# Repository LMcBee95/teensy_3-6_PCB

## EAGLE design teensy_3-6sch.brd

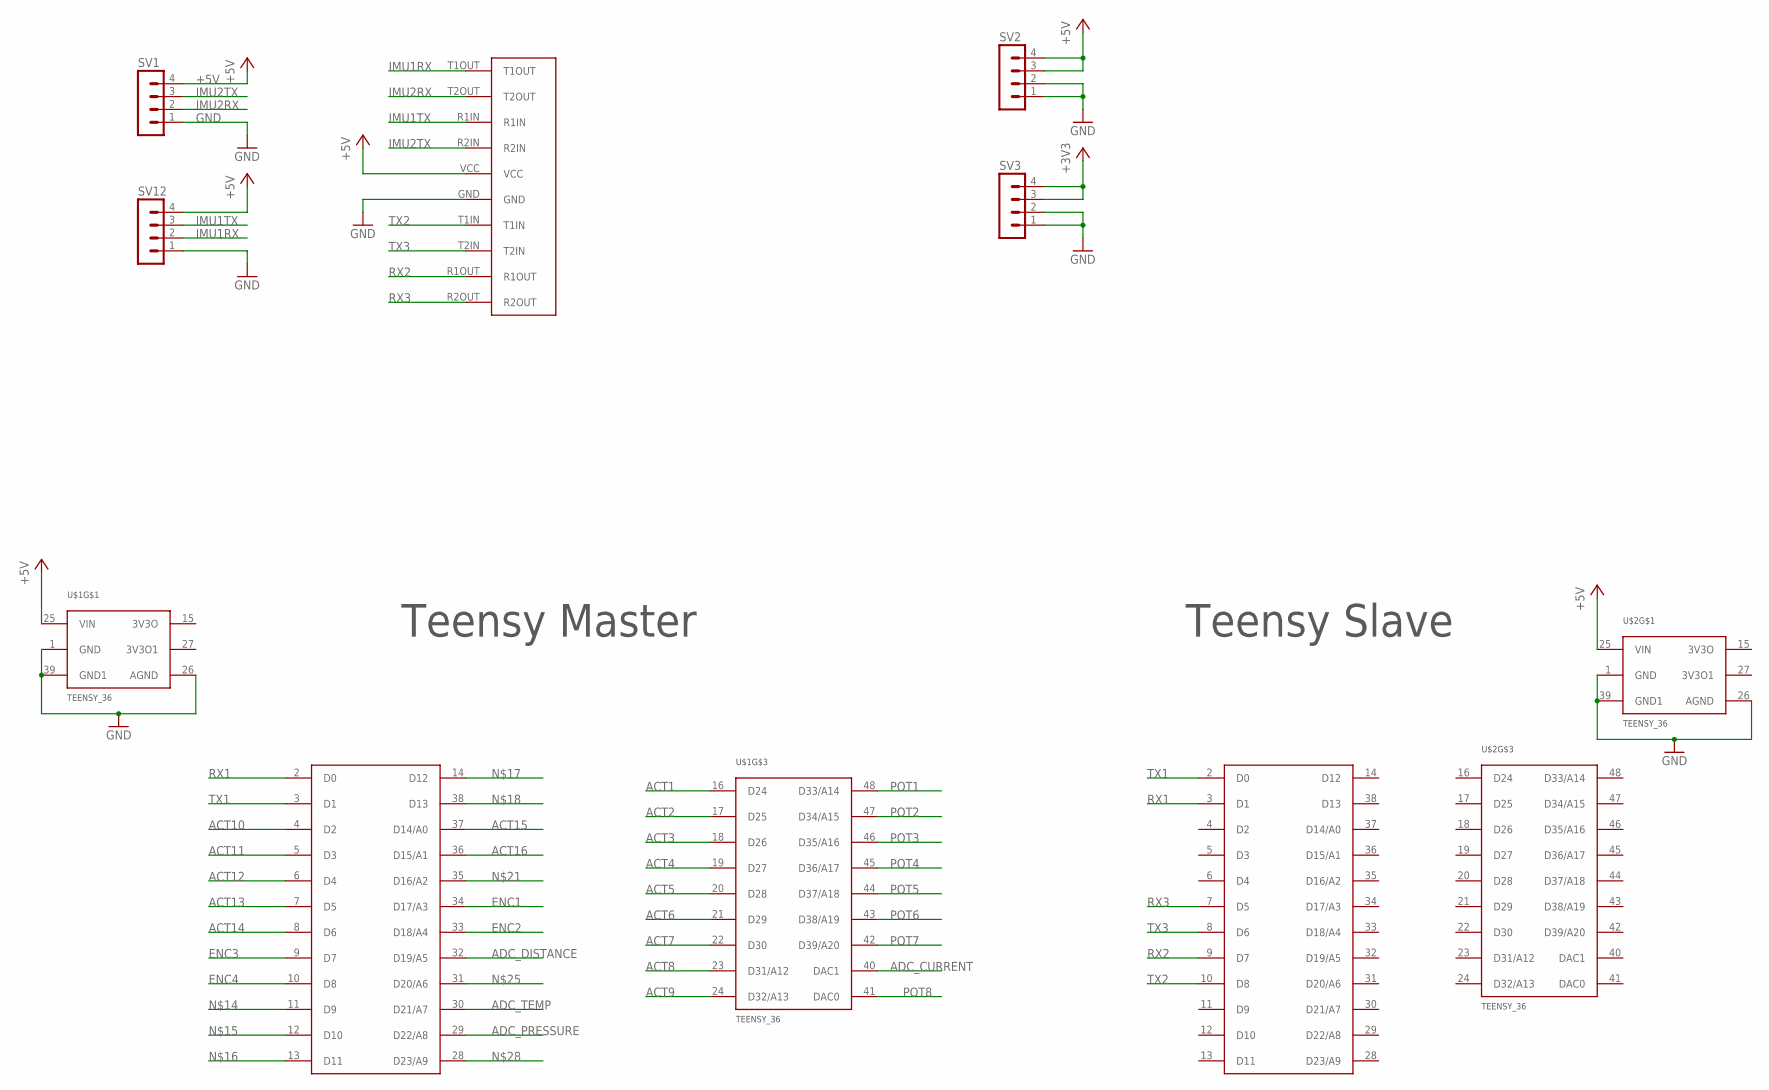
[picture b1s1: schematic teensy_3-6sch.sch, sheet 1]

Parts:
SV1, SV2, SV3, SV12: MA04-1
U$1, U$2: TEENSY_36; TEENSY36
U$3: MAX232_BREAKOUT

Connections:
+3V3: SV3.3, SV3.4; also elsewhere on the board
+5V: SV1.4, SV2.3, SV2.4, SV12.4, U$1.25 (VIN), U$2.25 (VIN), U$3.VCC; also elsewhere on the board
ACT1: U$1.16 (D24); also elsewhere on the board
ACT2: U$1.17 (D25); also elsewhere on the board
ACT3: U$1.18 (D26); also elsewhere on the board
ACT4: U$1.19 (D27); also elsewhere on the board
ACT5: U$1.20 (D28); also elsewhere on the board
ACT6: U$1.21 (D29); also elsewhere on the board
ACT7: U$1.22 (D30); also elsewhere on the board
ACT8: U$1.23 (D31/A12); also elsewhere on the board
ACT9: U$1.24 (D32/A13); also elsewhere on the board
ACT10: U$1.4 (D2); also elsewhere on the board
ACT11: U$1.5 (D3); also elsewhere on the board
ACT12: U$1.6 (D4); also elsewhere on the board
ACT13: U$1.7 (D5); also elsewhere on the board
ACT14: U$1.8 (D6); also elsewhere on the board
ACT15: U$1.37 (D14/A0); also elsewhere on the board
ACT16: U$1.36 (D15/A1); also elsewhere on the board
ADC_CURRENT: U$1.40 (DAC1); also elsewhere on the board
ADC_DISTANCE: U$1.32 (D19/A5); also elsewhere on the board
ADC_PRESSURE: U$1.29 (D22/A8); also elsewhere on the board
ADC_TEMP: U$1.30 (D21/A7); also elsewhere on the board
ENC1: U$1.34 (D17/A3); also elsewhere on the board
ENC2: U$1.33 (D18/A4); also elsewhere on the board
ENC3: U$1.9 (D7); also elsewhere on the board
ENC4: U$1.10 (D8); also elsewhere on the board
GND: SV1.1, SV2.1, SV2.2, SV3.1, SV3.2, SV12.1, U$1.1 (GND), U$1.26 (AGND), U$1.39 (GND1), U$2.1 (GND), U$2.26 (AGND), U$2.39 (GND1), U$3.GND; also elsewhere on the board
IMU1RX: SV12.2, U$3.T1OUT
IMU1TX: SV12.3, U$3.R1IN
IMU2RX: SV1.2, U$3.T2OUT
IMU2TX: SV1.3, U$3.R2IN
POT1: U$1.48 (D33/A14); also elsewhere on the board
POT2: U$1.47 (D34/A15); also elsewhere on the board
POT3: U$1.46 (D35/A16); also elsewhere on the board
POT4: U$1.45 (D36/A17); also elsewhere on the board
POT5: U$1.44 (D37/A18); also elsewhere on the board
POT6: U$1.43 (D38/A19); also elsewhere on the board
POT7: U$1.42 (D39/A20); also elsewhere on the board
POT8: U$1.41 (DAC0); also elsewhere on the board
RX1: U$1.2 (D0), U$2.3 (D1)
RX2: U$2.9 (D7), U$3.R1OUT
RX3: U$2.7 (D5), U$3.R2OUT
TX1: U$1.3 (D1), U$2.2 (D0)
TX2: U$2.10 (D8), U$3.T1IN
TX3: U$2.8 (D6), U$3.T2IN

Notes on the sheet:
Teensy Master
Teensy Slave

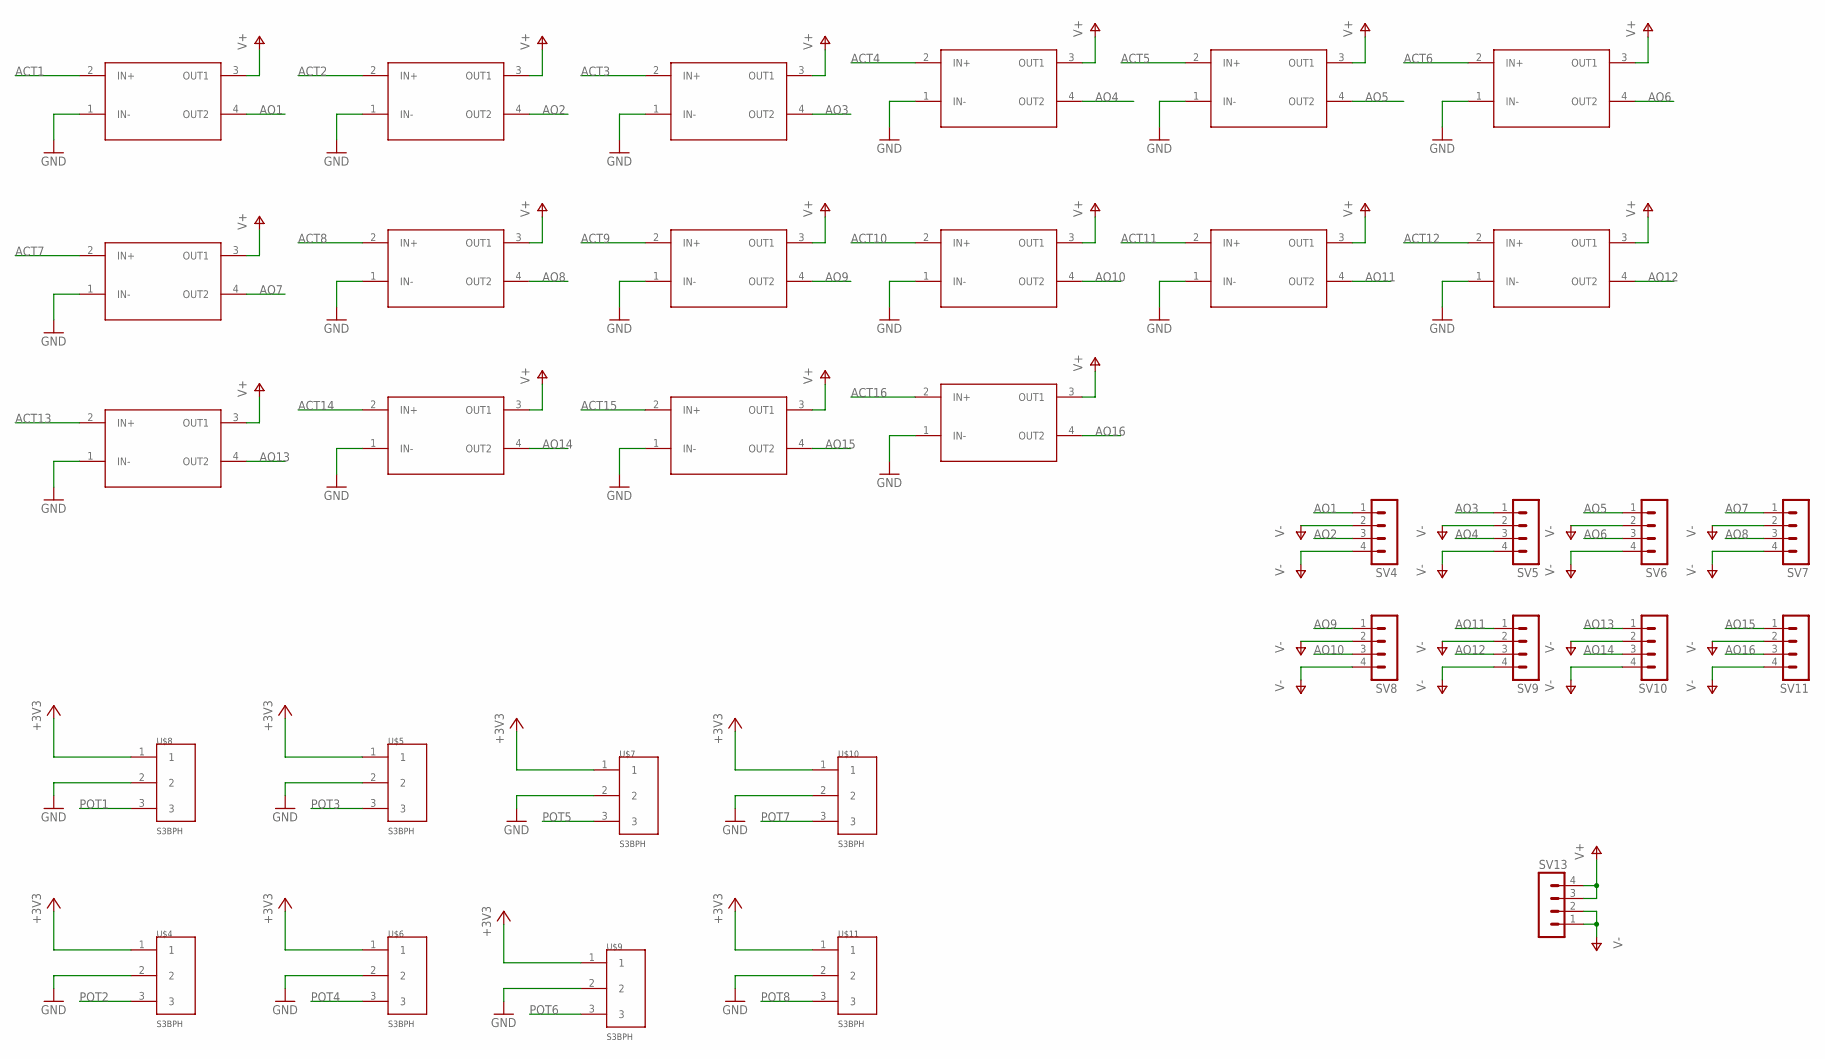
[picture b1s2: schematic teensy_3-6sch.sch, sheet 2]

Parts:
SV4, SV5, SV6, SV7, SV8, SV9, SV10, SV11, SV13: MA04-1
U$4, U$5, U$6, U$7, U$8, U$9, U$10, U$11: S3BPH
U$12, U$13, U$14, U$15, U$16, U$17, U$18, U$19, U$20, U$21, U$22, U$23, U$24, U$25, U$26, U$27: CPC1706

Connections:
+3V3: U$4.1, U$5.1, U$6.1, U$7.1, U$8.1, U$9.1, U$10.1, U$11.1; also elsewhere on the board
ACT1: U$12.2 (IN+); also elsewhere on the board
ACT2: U$13.2 (IN+); also elsewhere on the board
ACT3: U$14.2 (IN+); also elsewhere on the board
ACT4: U$15.2 (IN+); also elsewhere on the board
ACT5: U$16.2 (IN+); also elsewhere on the board
ACT6: U$17.2 (IN+); also elsewhere on the board
ACT7: U$18.2 (IN+); also elsewhere on the board
ACT8: U$19.2 (IN+); also elsewhere on the board
ACT9: U$20.2 (IN+); also elsewhere on the board
ACT10: U$21.2 (IN+); also elsewhere on the board
ACT11: U$22.2 (IN+); also elsewhere on the board
ACT12: U$23.2 (IN+); also elsewhere on the board
ACT13: U$24.2 (IN+); also elsewhere on the board
ACT14: U$25.2 (IN+); also elsewhere on the board
ACT15: U$26.2 (IN+); also elsewhere on the board
ACT16: U$27.2 (IN+); also elsewhere on the board
AO1: SV4.1, U$12.4 (OUT2)
AO2: SV4.3, U$13.4 (OUT2)
AO3: SV5.1, U$14.4 (OUT2)
AO4: SV5.3, U$15.4 (OUT2)
AO5: SV6.1, U$16.4 (OUT2)
AO6: SV6.3, U$17.4 (OUT2)
AO7: SV7.1, U$18.4 (OUT2)
AO8: SV7.3, U$19.4 (OUT2)
AO9: SV8.1, U$20.4 (OUT2)
AO10: SV8.3, U$21.4 (OUT2)
AO11: SV9.1, U$22.4 (OUT2)
AO12: SV9.3, U$23.4 (OUT2)
AO13: SV10.1, U$24.4 (OUT2)
AO14: SV10.3, U$25.4 (OUT2)
AO15: SV11.1, U$26.4 (OUT2)
AO16: SV11.3, U$27.4 (OUT2)
GND: U$4.2, U$5.2, U$6.2, U$7.2, U$8.2, U$9.2, U$10.2, U$11.2, U$12.1 (IN-), U$13.1 (IN-), U$14.1 (IN-), U$15.1 (IN-), U$16.1 (IN-), U$17.1 (IN-), U$18.1 (IN-), U$19.1 (IN-), U$20.1 (IN-), U$21.1 (IN-), U$22.1 (IN-), U$23.1 (IN-), U$24.1 (IN-), U$25.1 (IN-), U$26.1 (IN-), U$27.1 (IN-); also elsewhere on the board
POT1: U$8.3; also elsewhere on the board
POT2: U$4.3; also elsewhere on the board
POT3: U$5.3; also elsewhere on the board
POT4: U$6.3; also elsewhere on the board
POT5: U$7.3; also elsewhere on the board
POT6: U$9.3; also elsewhere on the board
POT7: U$10.3; also elsewhere on the board
POT8: U$11.3; also elsewhere on the board
V+: SV13.3, SV13.4, U$12.3 (OUT1), U$13.3 (OUT1), U$14.3 (OUT1), U$15.3 (OUT1), U$16.3 (OUT1), U$17.3 (OUT1), U$18.3 (OUT1), U$19.3 (OUT1), U$20.3 (OUT1), U$21.3 (OUT1), U$22.3 (OUT1), U$23.3 (OUT1), U$24.3 (OUT1), U$25.3 (OUT1), U$26.3 (OUT1), U$27.3 (OUT1)
V-: SV4.2, SV4.4, SV5.2, SV5.4, SV6.2, SV6.4, SV7.2, SV7.4, SV8.2, SV8.4, SV9.2, SV9.4, SV10.2, SV10.4, SV11.2, SV11.4, SV13.1, SV13.2

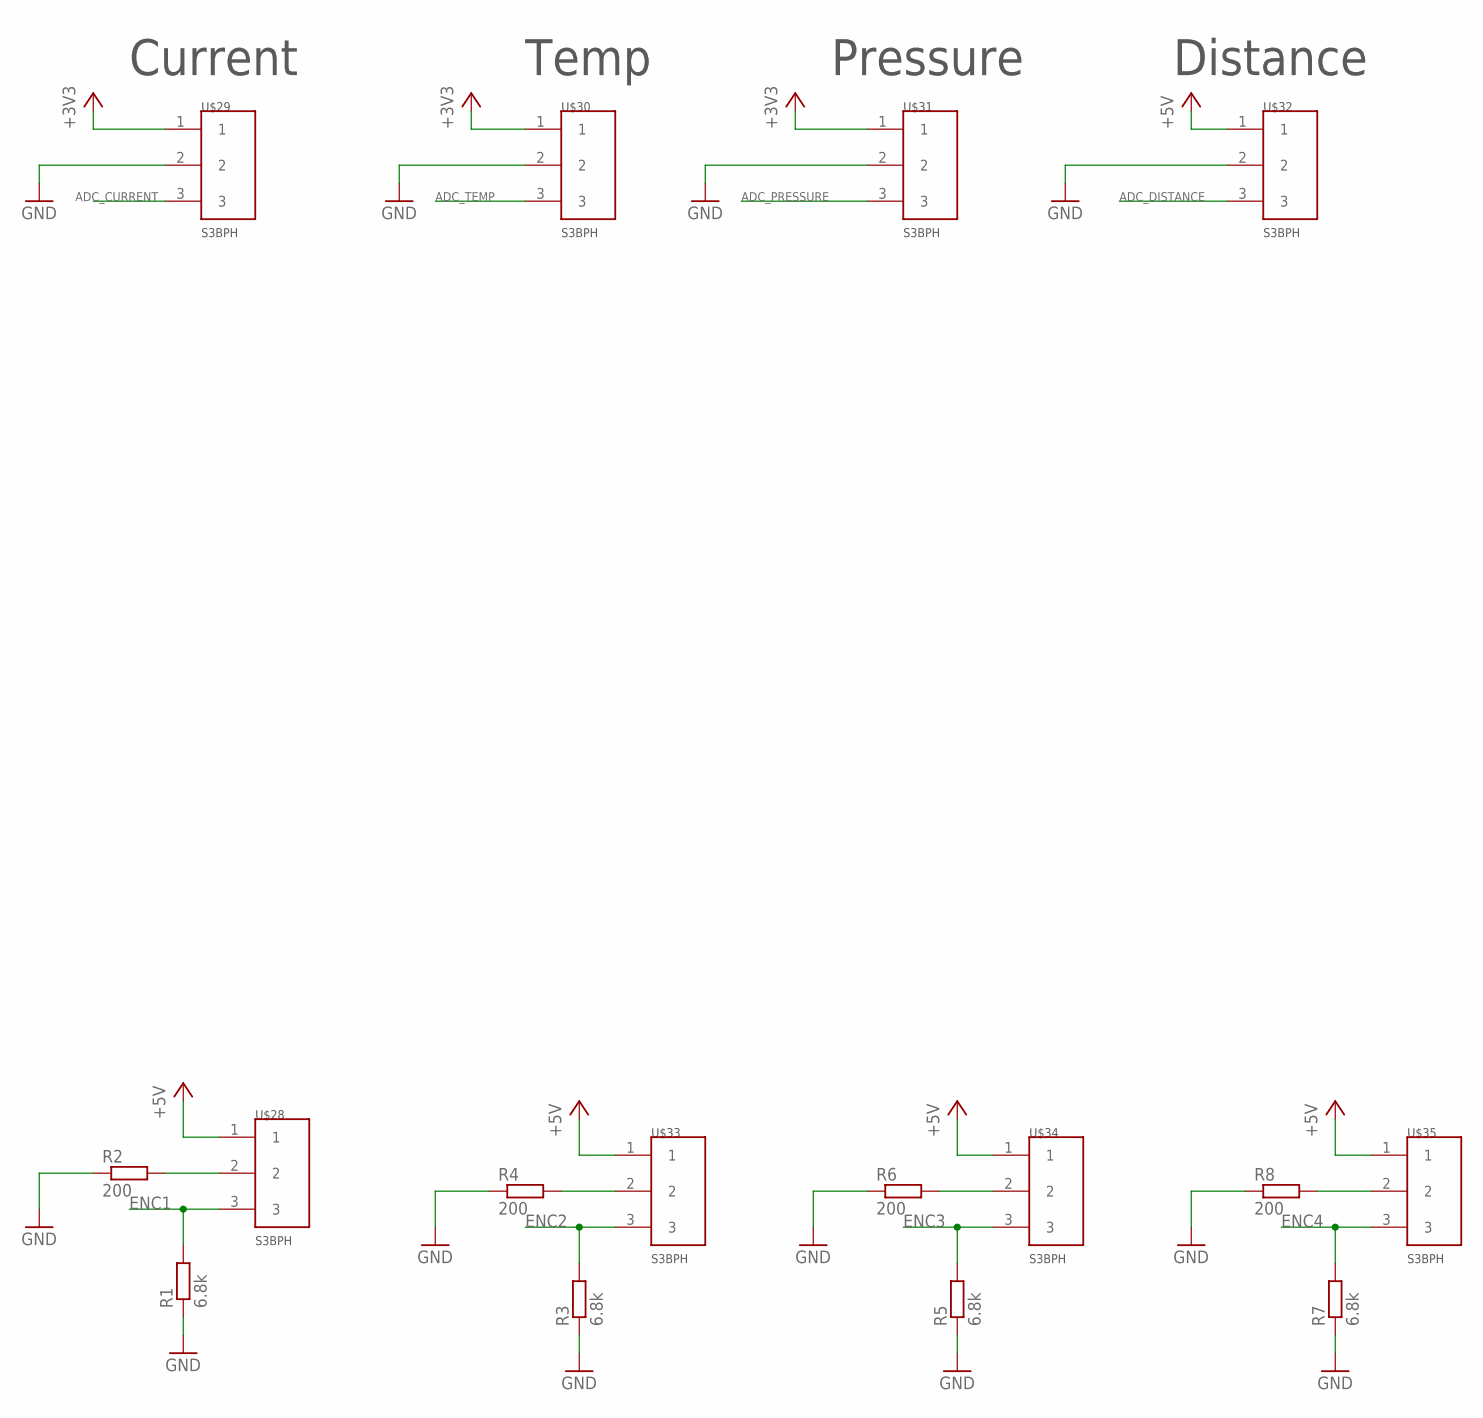
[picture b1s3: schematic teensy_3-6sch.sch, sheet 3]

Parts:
R1, R3, R5, R7: 6.8k; M0805
R2, R4, R6, R8: 200; M0805
U$28, U$29, U$30, U$31, U$32, U$33, U$34, U$35: S3BPH

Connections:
+3V3: U$29.1, U$30.1, U$31.1; also elsewhere on the board
+5V: U$28.1, U$32.1, U$33.1, U$34.1, U$35.1; also elsewhere on the board
ADC_CURRENT: U$29.3; also elsewhere on the board
ADC_DISTANCE: U$32.3; also elsewhere on the board
ADC_PRESSURE: U$31.3; also elsewhere on the board
ADC_TEMP: U$30.3; also elsewhere on the board
ENC1: R1.2, U$28.3; also elsewhere on the board
ENC2: R3.2, U$33.3; also elsewhere on the board
ENC3: R5.2, U$34.3; also elsewhere on the board
ENC4: R7.2, U$35.3; also elsewhere on the board
GND: R1.1, R2.1, R3.1, R4.1, R5.1, R6.1, R7.1, R8.1, U$29.2, U$30.2, U$31.2, U$32.2; also elsewhere on the board
unnamed: R2.2, U$28.2
unnamed: R4.2, U$33.2
unnamed: R6.2, U$34.2
unnamed: R8.2, U$35.2

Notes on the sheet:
Current
Temp
Pressure
Distance

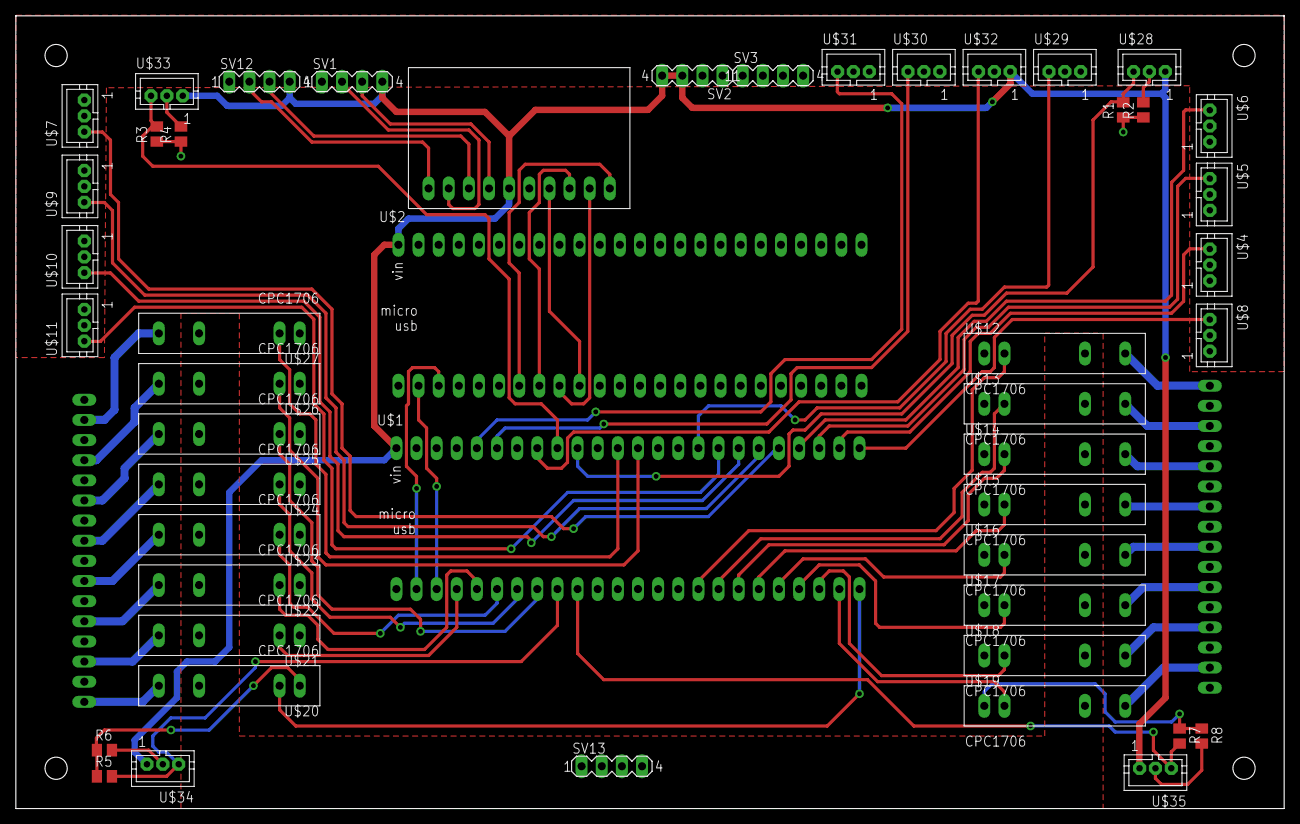
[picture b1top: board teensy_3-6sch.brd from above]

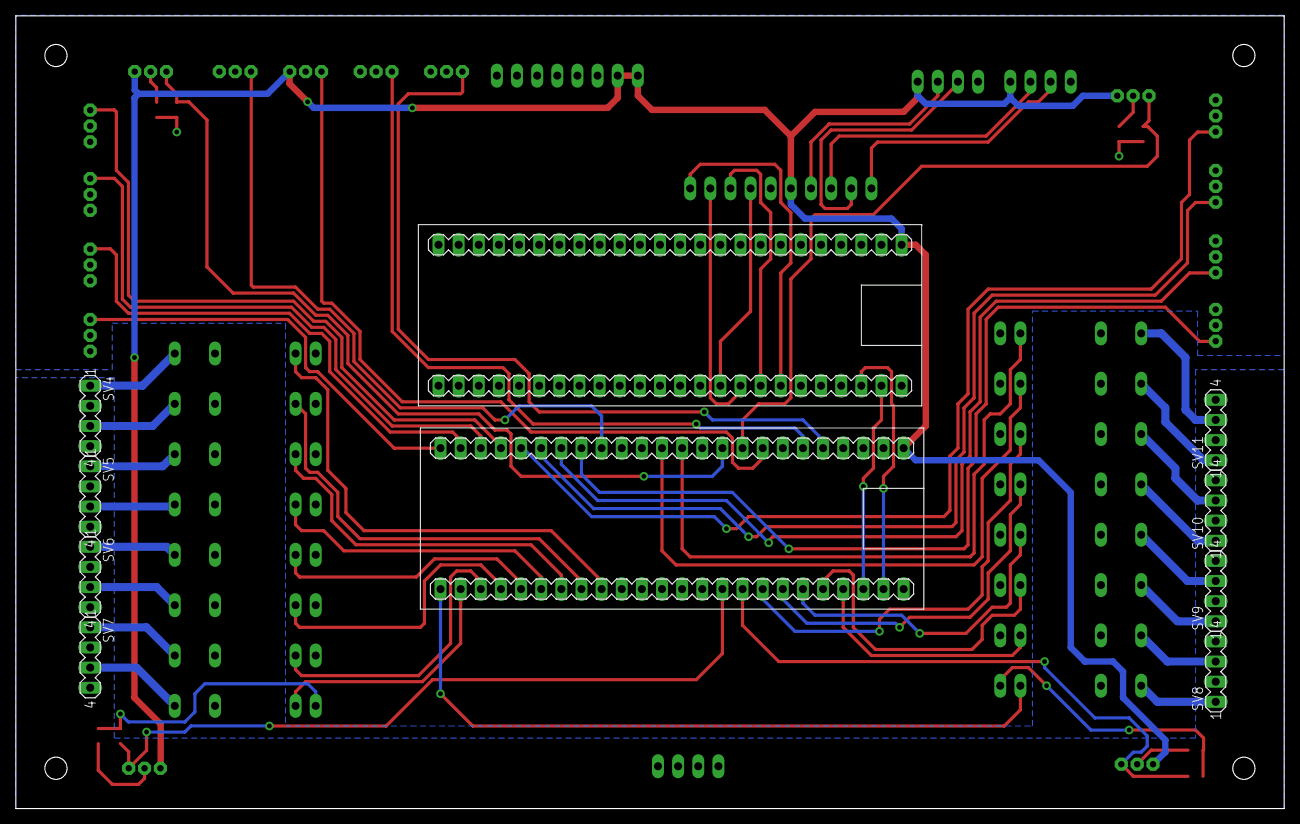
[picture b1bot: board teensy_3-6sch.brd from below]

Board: 2 copper layers, 160.0 x 100.0 mm, 56 parts (8 on the bottom side), 67 nets.

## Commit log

2016-12-23 Routed everything
